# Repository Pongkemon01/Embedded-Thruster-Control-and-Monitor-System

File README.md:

# Embedded-Thruster-Control-and-Monitor-System

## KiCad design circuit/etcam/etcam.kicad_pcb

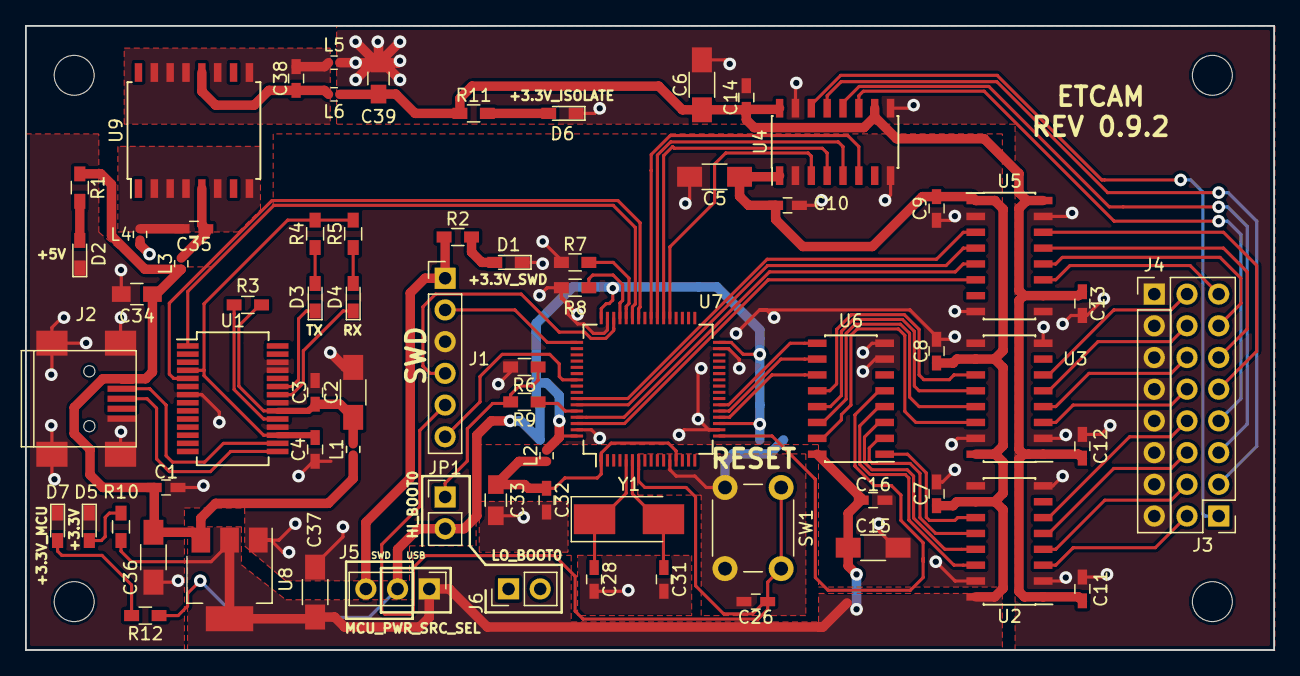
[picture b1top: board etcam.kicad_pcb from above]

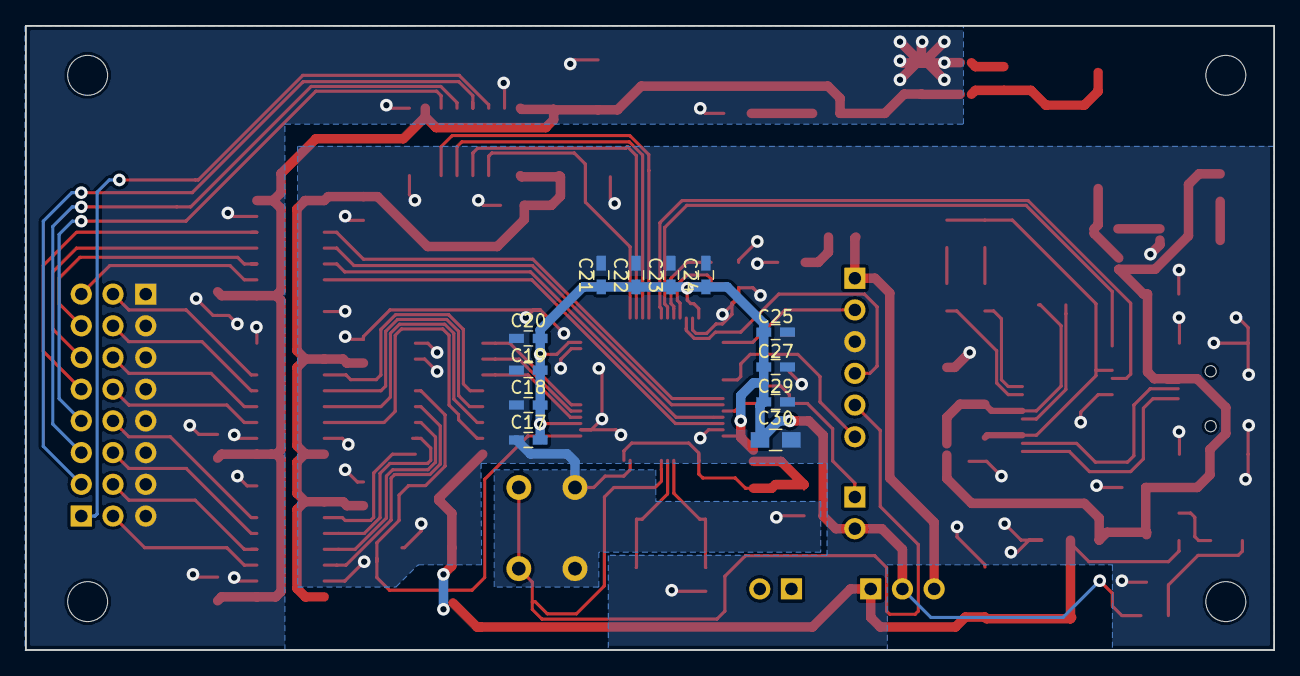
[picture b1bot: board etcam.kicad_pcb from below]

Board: 2 copper layers, 100.0 x 50.0 mm, 82 parts (12 on the bottom side), 74 nets.

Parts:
C1: 0.01uF; C_0603_HandSoldering
C2: 4.7uF; C_1206_HandSoldering
C3, C4, C7, C8, C9, C10, C11, C12, C13, C14, C16, C17, C18, C19, C20, C21, C22, C23, C24, C25, C26, C27, C29, C35: 0.1uF; C_0603_HandSoldering
C5, C6, C15: 1uF; C_1206_HandSoldering
C28, C31: 22pF; C_0603_HandSoldering
C30: 4.7uF; C_0805_HandSoldering
C32: 10nF; C_0603_HandSoldering
C33: 1uF; C_0805_HandSoldering
C34, C39: 10uF; C_0805_HandSoldering
C36, C37: 10uF; C_1206_HandSoldering
C38: 0.22uF; C_0603_HandSoldering
D1: +3.3V_SWD_LED; LED_0603_HandSoldering
D2: +5V_USB_LED; LED_0603_HandSoldering
D3: TX_LED; LED_0603_HandSoldering
D4: RX_LED; LED_0603_HandSoldering
D5: +3.3V_USB_LED; LED_0603_HandSoldering
D6: +3.3V_ISOLATOR_LED; LED_0603_HandSoldering
D7: +3.3V_CONTROLLER_LED; LED_0603_HandSoldering
J1: SWD_connector; Pin_Header_Straight_1x06_Pitch2.54mm
J2: USB_connector; USB_Mini-B
J3: ESC_signal_connector; Pin_Header_Straight_2x08_Pitch2.54mm
J4: ESC_GND_connector; Pin_Header_Straight_1x08_Pitch2.54mm
J5: MCU_PWR_SRC_selector; Pin_Header_Straight_1x03_Pitch2.54mm
J6: jumper_park; Pin_Header_Straight_1x02_Pitch2.54mm
JP1: BOOT_MODE_selector; Pin_Header_Straight_1x02_Pitch2.54mm
L1, L2, L3, L4, L5, L6: BLM15HD182SN1; L_0402
R1: 1k; R_0603_HandSoldering
R2, R4, R5, R10, R11, R12: 330; R_0603_HandSoldering
R3, R6, R7, R8, R9: 10k; R_0603_HandSoldering
SW1: reset_SW; SW_PUSH_6mm
U1: FT232RL; SSOP-28_5.3x10.2mm_Pitch0.65mm
U2, U3, U4, U5: Si8640BB-B-IS1; SOIC-16_3.9x9.9mm_Pitch1.27mm
U6: 74HC251; SOIC-16_3.9x9.9mm_Pitch1.27mm
U7: STM32F303xD/E-LQFP64; LQFP-64_10x10mm_Pitch0.5mm
U8: LM1117-3.3; SOT-223-3_TabPin2
U9: ADuM5020; SOIC-16W_7.5x10.3mm_Pitch1.27mm
Y1: 8MHz; Crystal_SMD_Abracon_ABM3-2pin_5.0x3.2mm_HandSoldering

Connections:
/+3.3V_ISOLATOR: C6.1, C11.1, C12.1, C13.1, C14.1, C39.1, L5.2, R11.1, U2.1, U3.1, U4.10, U4.16, U5.10, U5.16
/+3.3V_SWD: J1.1, J5.3, R2.1
/+3.3V_USB: C5.1, C7.1, C8.1, C9.1, C10.1, C15.1, C16.1, C37.1, J5.1, R10.1, U2.10, U2.16, U3.10, U3.16, U4.1, U5.1, U6.16, U8.2
/+5V_USB: C1.1, C34.1, C36.1, J2.1, L1.1, L3.1, R1.1, U8.3
/FTDI-->MCU: U1.1, U7.43
/FTDI<--MCU: U1.5, U7.42
/ISOLATED_DSHOT1: J3.1, U4.14
/ISOLATED_DSHOT2: J3.3, U4.13
/ISOLATED_DSHOT3: J3.5, U4.12
/ISOLATED_DSHOT4: J3.7, U4.11
/ISOLATED_DSHOT5: J3.9, U5.14
/ISOLATED_DSHOT6: J3.11, U5.13
/ISOLATED_DSHOT7: J3.13, U5.12
/ISOLATED_DSHOT8: J3.15, U5.11
/ISOLATED_TELEMETRY1: J3.2, U2.3
/ISOLATED_TELEMETRY2: J3.4, U2.4
/ISOLATED_TELEMETRY3: J3.6, U2.5
/ISOLATED_TELEMETRY4: J3.8, U2.6
/ISOLATED_TELEMETRY5: J3.10, U3.3
/ISOLATED_TELEMETRY6: J3.12, U3.4
/ISOLATED_TELEMETRY7: J3.14, U3.5
/ISOLATED_TELEMETRY8: J3.16, U3.6
/TDO_SWO: J1.6, U7.55
/TMS_SWCLK: J1.2, U7.49
/TMS_SWDIO: J1.4, U7.46
/controller/+3.3V_ANALOG: C32.1, C33.1, L2.2, U7.1, U7.13
/controller/+3.3V_CONTROLLER: C17.1, C18.1, C19.1, C20.1, C21.1, C22.1, C23.1, C24.1, C25.1, C27.1, C29.1, C30.1, J5.2, JP1.2, L2.1, R12.1, U7.19, U7.32, U7.48, U7.64
/controller/BOOT0: JP1.1, R6.1, R9.2
/controller/DSHOT1: U4.3, U7.37
/controller/DSHOT2: U4.4, U7.38
/controller/DSHOT3: U4.5, U7.39
/controller/DSHOT4: U4.6, U7.40
/controller/DSHOT5: U5.3, U7.58
/controller/DSHOT6: U5.4, U7.59
/controller/DSHOT7: U5.5, U7.61
/controller/DSHOT8: U5.6, U7.62
/controller/TELEMETRY_SEL0: U6.11, U7.20
/controller/TELEMETRY_SEL1: U6.10, U7.21
/controller/TELEMETRY_SEL2: U6.9, U7.22
/isolation_barrier/TELEMETRY1: U2.14, U6.4
/isolation_barrier/TELEMETRY2: U2.13, U6.3
/isolation_barrier/TELEMETRY3: U2.12, U6.2
/isolation_barrier/TELEMETRY4: U2.11, U6.1
/isolation_barrier/TELEMETRY5: U3.14, U6.15
/isolation_barrier/TELEMETRY6: U3.13, U6.14
/isolation_barrier/TELEMETRY7: U3.12, U6.13
/isolation_barrier/TELEMETRY8: U3.11, U6.12
/telementry_selector/SELECTED_TELEMETRY: U6.5, U7.17
/usb_to_serial/+3.3V_FTDI: C4.1, R4.2, R5.2, U1.4, U1.17
/usb_to_serial/+5V_FTDI: C2.1, C3.1, L1.2, R3.2, U1.20
/usb_to_serial/DM: J2.2, U1.16
/usb_to_serial/DP: J2.3, U1.15
/~RST: C26.1, J1.5, SW1.1, U7.7
GND: C1.2, C2.2, C3.2, C4.2, C5.2, C7.2, C8.2, C9.2, C10.2, C15.2, C16.2, C17.2, C18.2, C19.2, C20.2, C21.2, C22.2, C23.2, C24.2, C25.2, C26.2, C27.2, C28.2, C29.2, C30.2, C31.2, C32.2, C33.2, C34.2, C36.2, C37.2, D1.1, D2.1, D5.1, D7.1, J1.3, J2.5, J2.6, L4.1, R6.2, R7.1, R8.1, SW1.2, U1.7, U1.18, U1.21, U1.25, U1.26, U2.9, U2.15, U3.9, U3.15, U4.2, U4.8, U5.2, U5.8, U6.7, U6.8, U7.12, U7.18, U7.31, U7.47, U7.63, U8.1
GNDPWR: C6.2, C11.2, C12.2, C13.2, C14.2, C39.2, D6.1, J4.1, J4.2, J4.3, J4.4, J4.5, J4.6, J4.7, J4.8, L6.2, U2.2, U2.8, U3.2, U3.8, U4.9, U4.15, U5.9, U5.15
unnamed: C28.1, U7.5, Y1.1
unnamed: C31.1, U7.6, Y1.2
unnamed: C35.1, L3.2, U9.5
unnamed: C35.2, L4.2, U9.2, U9.3, U9.4, U9.6, U9.8
unnamed: C38.1, L5.1, U9.12
unnamed: C38.2, L6.1, U9.9, U9.11, U9.13, U9.14, U9.15
unnamed: D1.2, R2.2
unnamed: D2.2, R1.2
unnamed: D3.1, U1.23
unnamed: D3.2, R4.1
unnamed: D4.1, U1.22
unnamed: D4.2, R5.1
unnamed: D5.2, R10.2
unnamed: D6.2, R11.2
unnamed: D7.2, R12.2
unnamed: R3.1, U1.19
unnamed: R7.2, U7.44
unnamed: R8.2, U7.45
unnamed: R9.1, U7.60

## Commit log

2018-11-27 init Embedded-Thruster-Control-and-Monitor-System repository
2018-11-27 added gitignore for KiCad
2018-11-29 init ETCAM_for_nucleo_32 KiCad project
2018-11-29 init ETCAM_lib and added 74HC251 to ETCAM_lib
2018-11-29 fixed component name from '74HS251' to '74HC251'
2018-11-29 deleted 74HS251 from ETCAM_lib
2018-11-29 changed appearance of 74HC251 component
2018-11-29 added SI8660BA-B-IS1 component from zeabus_lib to ETCAM_lib
2018-11-30 added Nucleo-32 component to ETCAM_lib
2018-11-30 reversed .gitignore for '*-cache.lib' ignoring
2018-11-30 added Nucleo-32 and 74HC251 to etcam_for_nucleo_32
2018-11-30 removed Si8660BA-B-IS1 and added Si8640BB-B-IS1 to ETCAM_lib
2018-11-30 added digital isolators into ETCAM_for_Nucleo_32
2018-11-30 annotated ETCAM_for_Nucleo_32 and fixed error from ERC
2018-11-30 added footprints to components in ETCAM_for_Nucleo_32
2018-11-30 created Nucleo-32 footprint and added etcam.pretty
2018-11-30 added ETCAM footprint lib to ETCAM_for_Nucleo_32
2018-11-30 fixed pin number of Nucleo-32 footprint
2018-11-30 fixed Nucleo-32 component pin number and footprint
2018-11-30 changed 'ETCAM_lib' to 'ETCAM'
2018-12-01 deleted silk mark on Nucleo-32 footprint
2018-12-01 fixed Nucleo-32 footprint using Nucleo-32 mechanical drawing
2018-12-01 moved 'REF**' of Nucleo-32 footprint
2018-12-01 added pin headers to ESCs
2018-12-01 changed 'ESC' labels to 'DSHOT'
2018-12-01 changed name of pin headers to ESCs
2018-12-18 added ADuM5020 to ETCAM
2018-12-18 added ADuM5020 to ETCAM_for_Nucleo_32
2018-12-18 added 1uF tantalum capacitors and changed 10uF footprint to 0805
2018-12-18 annotated ETCAM_for_Nucleo_32
2019-04-16 moved kicad-lib and schematic directory to circuit/
2019-04-16 added etcam kicad project
2019-04-16 added STM32F303xD/E-LQFN64 component symbol to etcam library
2019-04-16 added FT232RL component symbol to etcam library
2019-04-16 changed "NRST" pin name on STM32F303*D/E-LQFP64 symbol to "RST" with bar
2019-04-16 added FT232RL and completed power supply part for FT232RL and STM32F303xD/E
2019-04-17 completed pin layout on STM32F303xD/E in ETCAM
2019-04-17 added JTAG pin to STM32F303xD/E in ETCAM
2019-04-17 changed JTAG to SWD and added SWD connector in ETCAM
2019-04-18 simplified boot mode circuit
2019-04-18 made usb_to_serial circuit and controller circuit into separate sheet
2019-04-18 added isolation_barrier and telementry_selector to ETCAM
2019-04-18 rearrage symbols in isolation_barrier of ETCAM
2019-04-18 changed 100nF to 0.1uF in ETCAM
2019-04-18 assigned footprint to every component of ETCAM
2019-04-18 annotated components in ETCAM
2019-04-18 performed and corrected electrical rules check
2019-04-18 removed schematic_for_nucleo_32
2019-04-19 changed GND of reset_SW to GNDA in ETCAM
2019-04-19 added revision number to schematic sheet of ETCAM
2019-04-19 configured pcb design rules of ETCAM
2019-04-19 added LEDs to every power rail of ETCAM and re-annotated the schematic
2019-04-19 fixed USB-DP of STM32 don't connected to ground in ETCAM
2019-04-20 added LED for +3.3V in controller schematic of ETCAM
2019-04-20 finished routing ETCAM PCB without GND
2019-04-20 added mounting holes into ETCAM PCB
2019-04-20 added descriptive silkskins to ETCAM PCB
2019-04-20 added GND plane to ETCAM PCB
2019-04-20 added via between front and back GND plane in ETCAM PCB
2019-04-20 fixed +3.3V_ISOLATOR_LED grounded to GND in ETCAM
2019-04-20 added GNDPWR pland to ETCAM PCB
2019-04-20 fixed position of 3.3V_ISOLATOR_LED label in ETCAM PCB
2019-04-20 added ETCAM description into PCB
2019-04-20 fixed straight trace in ETCAM PCB
2019-04-20 fixed U7 reference to front side in ETCAM PCB
2019-04-21 moved .gitignore to circuit/
2019-04-21 created code/ and added .gitignore to code/
2019-04-21 init code of LED blink using FreeRTOS on NUCLEO-F303RE
2019-04-23 fixed "telementry" to "telemetry" in ETCAM
2019-04-23 fixed +3.3V_ISOLATOR cut GND_PWR plane in ETCAM PCB
2019-04-23 rearranged mounting holes of ETCAM PCB
2019-04-24 made /code into workspace approach
2019-04-24 fixed MCU_PWR_SRC_SEL silkskin in ETCAM PCB
2019-04-24 moved passive components of FTDI more nearer
2019-04-24 fixed TX_LED and RX_LED silkskin in ETCAM PCB
2019-04-24 made main.c into plain main
2019-04-29 could receive command via UART using DMA
2019-04-29 added grouping style into naming convection
2019-04-29 could parse throttle command into throttle in code/
2019-04-29 aligned left most operand in code/
2019-04-29 refactored init and error handler functions in code/
2019-04-30 better shared src management and sync between receiver and parser task
2019-04-30 fixed parameter name of msp init of uart in code/
2019-05-05 could make pulse from throttle command
2019-05-12 could write pulse to an IO pin
2019-05-12 removed addtional baud in output pulses
2019-05-12 made array of pulse dimension more readable
2019-05-13 changed thruster task tick rate into 1kHz
2019-05-13 removed led init function
2019-05-13 changed PLL clock into 72MHz
2019-05-13 could write pulse on TIM4's IO pin in code/
2019-05-13 refactored name of variables in code/
2019-05-13 refactored uart initialization from main.c to init.c in code/
2019-05-13 refactored timer initialization from main.c to init.c in code/
2019-05-13 refactored command tasks from main.c to task_command.c in code/
2019-05-13 refactored config definition from main.h to config.h in code/
2019-05-14 could write pulse on TIM8's pin in code/
2019-05-14 could write pulse on TIM16's pin in code/
2019-05-14 could write telemetry bit and receive telemetry
2019-05-14 could select telemetry channel in code/
2019-05-14 could transmit telemetry to control device in code/
2019-05-14 added synchronization to telemetry transmitter in code/
2019-05-17 swaped role between USART1 and USART2 in /code
2019-05-18 changed timeout of waiting for telemetry response to 40ms in code/
2019-05-18 made throttle bit reversed before be packed DSHOT in /code
2019-05-18 changed config.h to definition.h in code/
2019-05-18 added timeout to command receiving process
2019-05-18 fixed name of const telemetry begin variable in code/
2019-05-19 added timeout to telemetry receiving process
2019-05-19 made definition of task sleep time in /code
2019-05-19 decreased complexity of command parser task in code/
2019-05-19 made reverse_throttle_bit and generate_crc function inline in code/
2019-05-19 refactored peripheral initialization in code/
2019-05-19 refactored os element initialization from main.c into init.h in code/
2019-05-23 move ETCAM firmware to firmware/ in code/
2019-05-23 made name of dshot size defination describe it is bit size defination
2019-05-24 added libetcam, driver for ETCAM, in code/
2019-05-25 used pass by ref instead of pass by value in function of driver/
2019-05-26 made class declaration of ETCAM driver legit
2019-05-26 quitted using thruster state word in code/
2019-05-26 fixed member data name of TelemetrySync class in driver/
2019-05-27 corrected telemetry voltage and current parsing in driver/
2019-05-27 fixed typo of TelemetryStruct.us_power_consumption in driver/
2019-06-03 corrected telemetry erpm parsing in driver/
2019-06-03 removed default value from TelemetryStruct and u_sync_count in driver/
2019-06-03 fixed u_sync_count_ typo in driver/
2019-06-05 flush telemetry receive line before receiving process in firmware/
2019-06-15 added comment on flushing telemetry process in firmware/
2019-06-15 fixed the firmware stuck randomly in firmware/
